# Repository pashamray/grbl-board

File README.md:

# grbl-board
used:
Adafruit eagle library - https://github.com/adafruit/Adafruit-Eagle-Library

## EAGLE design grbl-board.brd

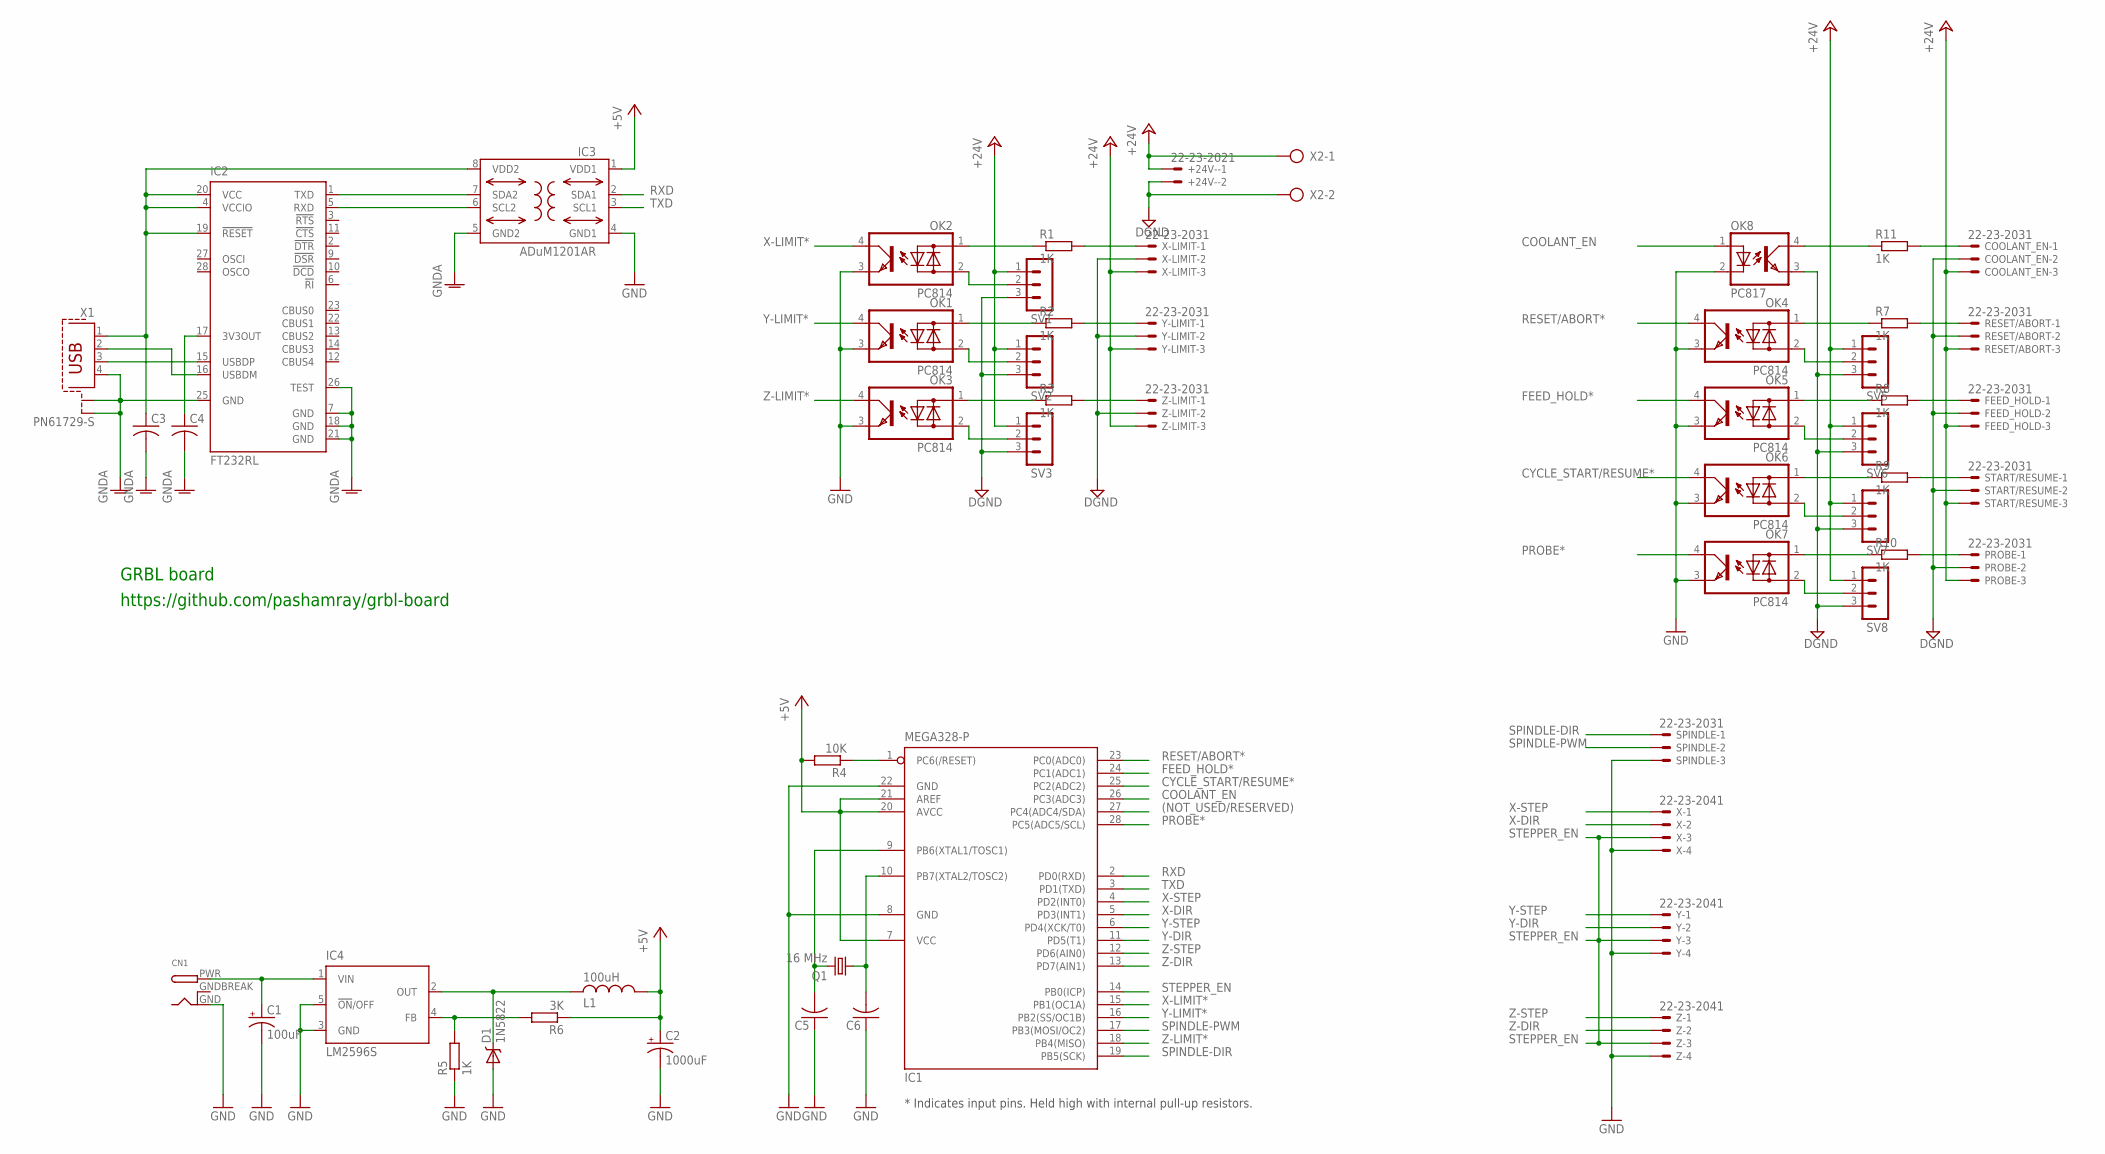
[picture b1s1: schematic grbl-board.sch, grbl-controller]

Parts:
+24V-: 22-23-2021
C1: 100uF; E5-6
C2: 1000uF; E5-10,5
C3, C4, C5, C6: C-USC0805K; C0805K
CN1: DCBARRELPTH; DCJACK_2MM_PTH
COOLANT_EN: 22-23-2031
D1: 1N5822; SMA-DIODE
FEED_HOLD: 22-23-2031
IC1: MEGA328-P; DIL28-3
IC2: FT232RL; SSOP28
IC3: ADuM1201AR; SO8-COOL
IC4: LM2596S; TO263-5
L1: 100uH; 1800R
OK1, OK2, OK3, OK4, OK5, OK6, OK7: PC814; DIL04
OK8: PC817; DIL04
PROBE: 22-23-2031
Q1: 16 MHz; HC49/S
R1, R2, R3, R5, R7, R8, R9, R10, R11: 1K; M0805
R4: 10K; M0805
R6: 3K; M0805
RESET/ABORT: 22-23-2031
SPINDLE: 22-23-2031
START/RESUME: 22-23-2031
SV1, SV2, SV3, SV5, SV6, SV7, SV8: MA03-1
X: 22-23-2041
X1: PN61729-S
X2: AK500/2
X-LIMIT: 22-23-2031
Y: 22-23-2041
Y-LIMIT: 22-23-2031
Z: 22-23-2041
Z-LIMIT: 22-23-2031

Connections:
(NOT_USED/RESERVED): IC1.27 (PC4(ADC4/SDA))
+5V: C2.+, IC1.7 (VCC), IC1.20 (AVCC), IC1.21 (AREF), IC3.1 (VDD1), L1.1, R4.2, R6.1
+24V: +24V-.1, COOLANT_EN.3, FEED_HOLD.3, PROBE.3, RESET/ABORT.3, START/RESUME.3, SV1.1, SV2.1, SV3.1, SV5.1, SV6.1, SV7.1, SV8.1, X2.1, X-LIMIT.3, Y-LIMIT.3, Z-LIMIT.3
COOLANT_EN: IC1.26 (PC3(ADC3)), OK8.1 (A)
CYCLE_START/RESUME*: IC1.25 (PC2(ADC2)), OK6.4 (C)
DGND: +24V-.2, COOLANT_EN.2, FEED_HOLD.2, OK8.3 (EMIT), PROBE.2, RESET/ABORT.2, START/RESUME.2, SV1.3, SV2.3, SV3.3, SV5.3, SV6.3, SV7.3, SV8.3, X2.2, X-LIMIT.2, Y-LIMIT.2, Z-LIMIT.2
FEED_HOLD*: IC1.24 (PC1(ADC1)), OK5.4 (C)
GND: C1.-, C2.-, C5.1, C6.1, CN1.GND, D1.A, IC1.8 (GND), IC1.22 (GND), IC3.4 (GND1), IC4.3 (GND), IC4.5 (!ON!/OFF), OK1.3 (E), OK2.3 (E), OK3.3 (E), OK4.3 (E), OK5.3 (E), OK6.3 (E), OK7.3 (E), OK8.2 (C), R5.1, SPINDLE.3, X.4, Y.4, Z.4
GNDA: C3.2, C4.2, IC2.7 (GND), IC2.18 (GND), IC2.21 (GND), IC2.25 (GND), IC2.26 (TEST), IC3.5 (GND2), X1.4, X1.S1, X1.S2
GNDBREAK: CN1.GNDBREAK
unnamed: IC2.1 (TXD), IC3.7 (SDA2)
unnamed: IC2.5 (RXD), IC3.6 (SCL2)
unnamed: IC2.16 (USBDM), X1.2
unnamed: IC2.15 (USBDP), X1.3
unnamed: OK2.1 (AC1), R1.1
unnamed: C5.2, IC1.9 (PB6(XTAL1/TOSC1)), Q1.2
unnamed: C6.2, IC1.10 (PB7(XTAL2/TOSC2)), Q1.1
unnamed: R2.2, Y-LIMIT.1
unnamed: R3.2, Z-LIMIT.1
unnamed: OK3.1 (AC1), R3.1
unnamed: OK3.2 (AC2), SV3.2
unnamed: OK2.2 (AC2), SV1.2
unnamed: R1.2, X-LIMIT.1
unnamed: OK1.2 (AC2), SV2.2
unnamed: OK1.1 (AC1), R2.1
unnamed: D1.C, IC4.2 (OUT), L1.2
unnamed: OK4.2 (AC2), SV5.2
unnamed: IC4.4 (FB), R5.2, R6.2
unnamed: C1.+, CN1.PWR, IC4.1 (VIN)
unnamed: OK4.1 (AC1), R7.1
unnamed: OK5.2 (AC2), SV6.2
unnamed: OK6.2 (AC2), SV7.2
unnamed: OK7.2 (AC2), SV8.2
unnamed: OK5.1 (AC1), R8.1
unnamed: OK6.1 (AC1), R9.1
unnamed: OK7.1 (AC1), R10.1
unnamed: PROBE.1, R10.2
unnamed: R9.2, START/RESUME.1
unnamed: FEED_HOLD.1, R8.2
unnamed: R7.2, RESET/ABORT.1
unnamed: C4.1, IC2.17 (3V3OUT)
unnamed: OK8.4 (COL), R11.1
unnamed: COOLANT_EN.1, R11.2
PROBE*: IC1.28 (PC5(ADC5/SCL)), OK7.4 (C)
RESET: IC1.1 (PC6(/RESET)), R4.1
RESET/ABORT*: IC1.23 (PC0(ADC0)), OK4.4 (C)
RXD: IC1.2 (PD0(RXD)), IC3.2 (SDA1)
SPINDLE-DIR: IC1.19 (PB5(SCK)), SPINDLE.1
SPINDLE-PWM: IC1.17 (PB3(MOSI/OC2)), SPINDLE.2
STEPPER_EN: IC1.14 (PB0(ICP)), X.3, Y.3, Z.3
TXD: IC1.3 (PD1(TXD)), IC3.3 (SCL1)
VDD2: C3.1, IC2.4 (VCCIO), IC2.19 (!RESET), IC2.20 (VCC), IC3.8 (VDD2), X1.1
X-DIR: IC1.5 (PD3(INT1)), X.2
X-LIMIT*: IC1.15 (PB1(OC1A)), OK2.4 (C)
X-STEP: IC1.4 (PD2(INT0)), X.1
Y-DIR: IC1.11 (PD5(T1)), Y.2
Y-LIMIT*: IC1.16 (PB2(SS/OC1B)), OK1.4 (C)
Y-STEP: IC1.6 (PD4(XCK/T0)), Y.1
Z-DIR: IC1.13 (PD7(AIN1)), Z.2
Z-LIMIT*: IC1.18 (PB4(MISO)), OK3.4 (C)
Z-STEP: IC1.12 (PD6(AIN0)), Z.1

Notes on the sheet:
* Indicates input pins. Held high with internal pull-up resistors.
https://github.com/pashamray/grbl-board
GRBL board

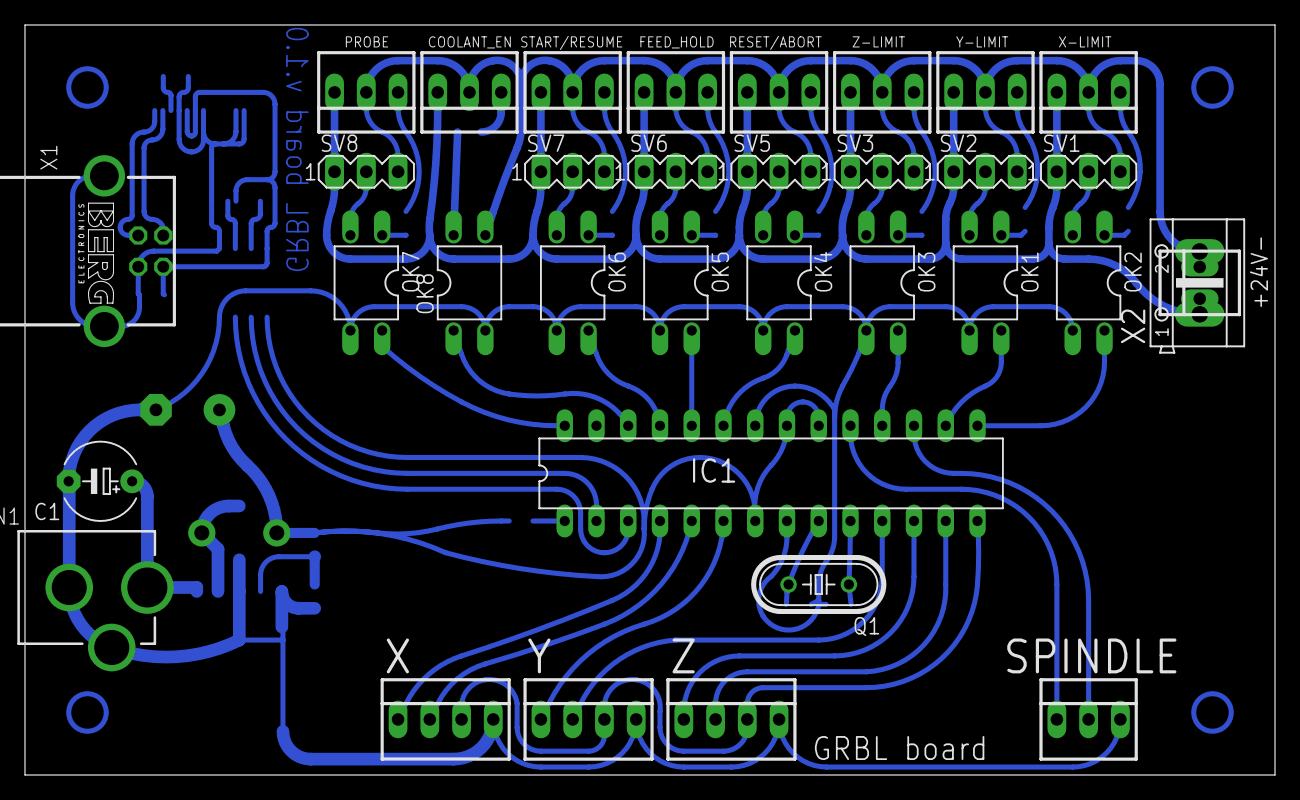
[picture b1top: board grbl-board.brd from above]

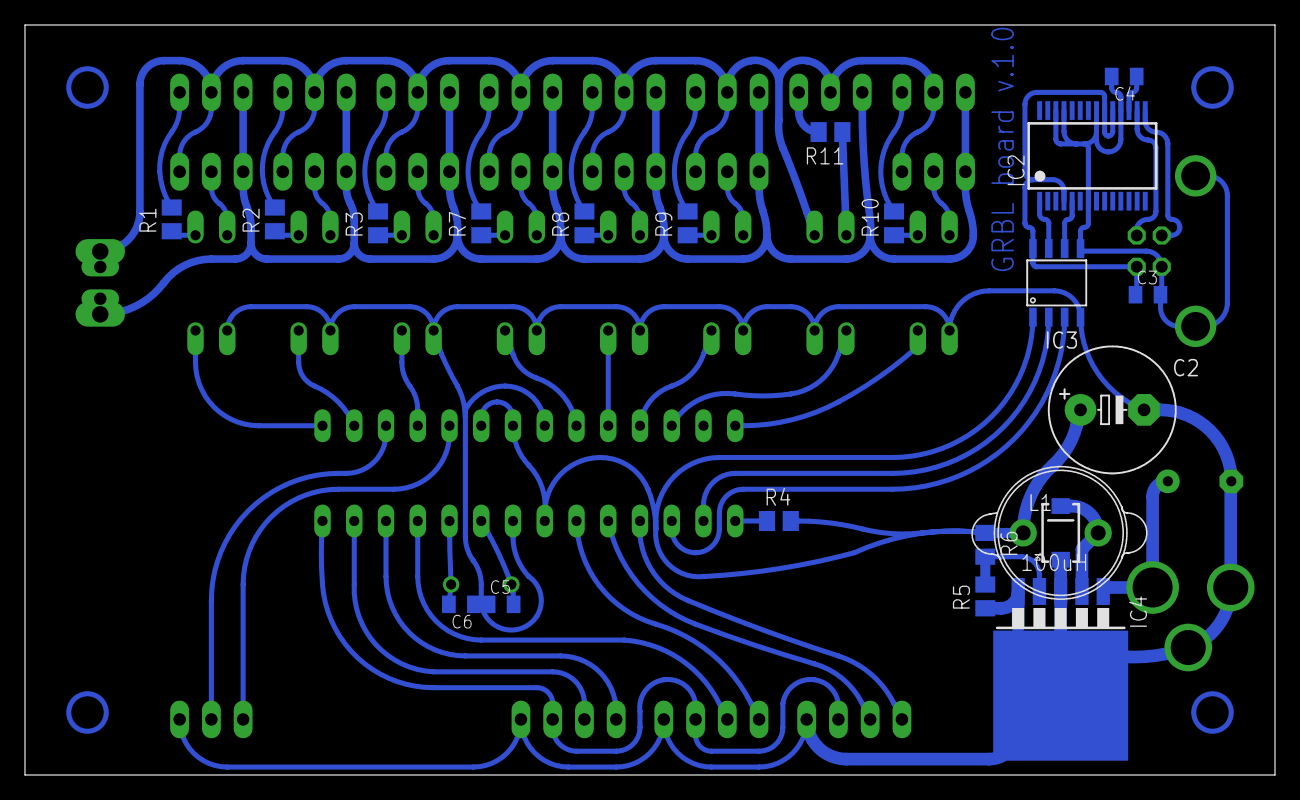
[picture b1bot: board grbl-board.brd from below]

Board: 2 copper layers, 100.0 x 60.0 mm, 55 parts (21 on the bottom side), 59 nets.

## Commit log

2016-01-06 add xyz-limits
2016-01-06 rename
2016-01-06 add arduino nano2
2016-01-07 add driver connectors
2016-01-07 add vreg add ISP
2016-01-07 add arduino from adafruit library
2016-01-07 add brd
2016-01-08 del arduino
2016-01-08 add buttons
2016-01-09 add spindle
2016-01-09 route power supply
2016-01-11 route round lines refactor
2016-01-12 rounded commit
2016-01-12 refactor
2016-01-12 ver.1.0
2016-03-25 size fonts

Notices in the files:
parts and their libraries:
SwK-SparkFun: Licensing: CC v3.0 Share-Alike You are welcome to use this library for commercial purposes.
